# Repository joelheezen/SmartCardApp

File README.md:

# SmartCardApp
App to add barcodes to a smartdevice

# reading the saved data
use sharedPreferences to get the StringSet this gets a list in the following format:

```
val sharedPref = activity?.getPreferences(Context.MODE_PRIVATE) ?:return
val L = sharedPref.getStringSet("barcodes", HashSet()) // L = ("name0|number0|format0", "name1|number1|format1", ...etc)
```

then split using a delimiter like so:

```
L.forEach{
    val str = it
    val delimiter = "|"
    val values = str.split(delimiter)
    values[0] = name
    values[1] = number
    values[2] = format
    }
```
 
# barcode formats

barcodes are returned as an int, so for example, EAN-13 is denoted as 32

https://developers.google.com/android/reference/com/google/mlkit/vision/barcode/common/Barcode#FORMAT_EAN_13

check the link for explanation and complete formats compatible with this scanner.

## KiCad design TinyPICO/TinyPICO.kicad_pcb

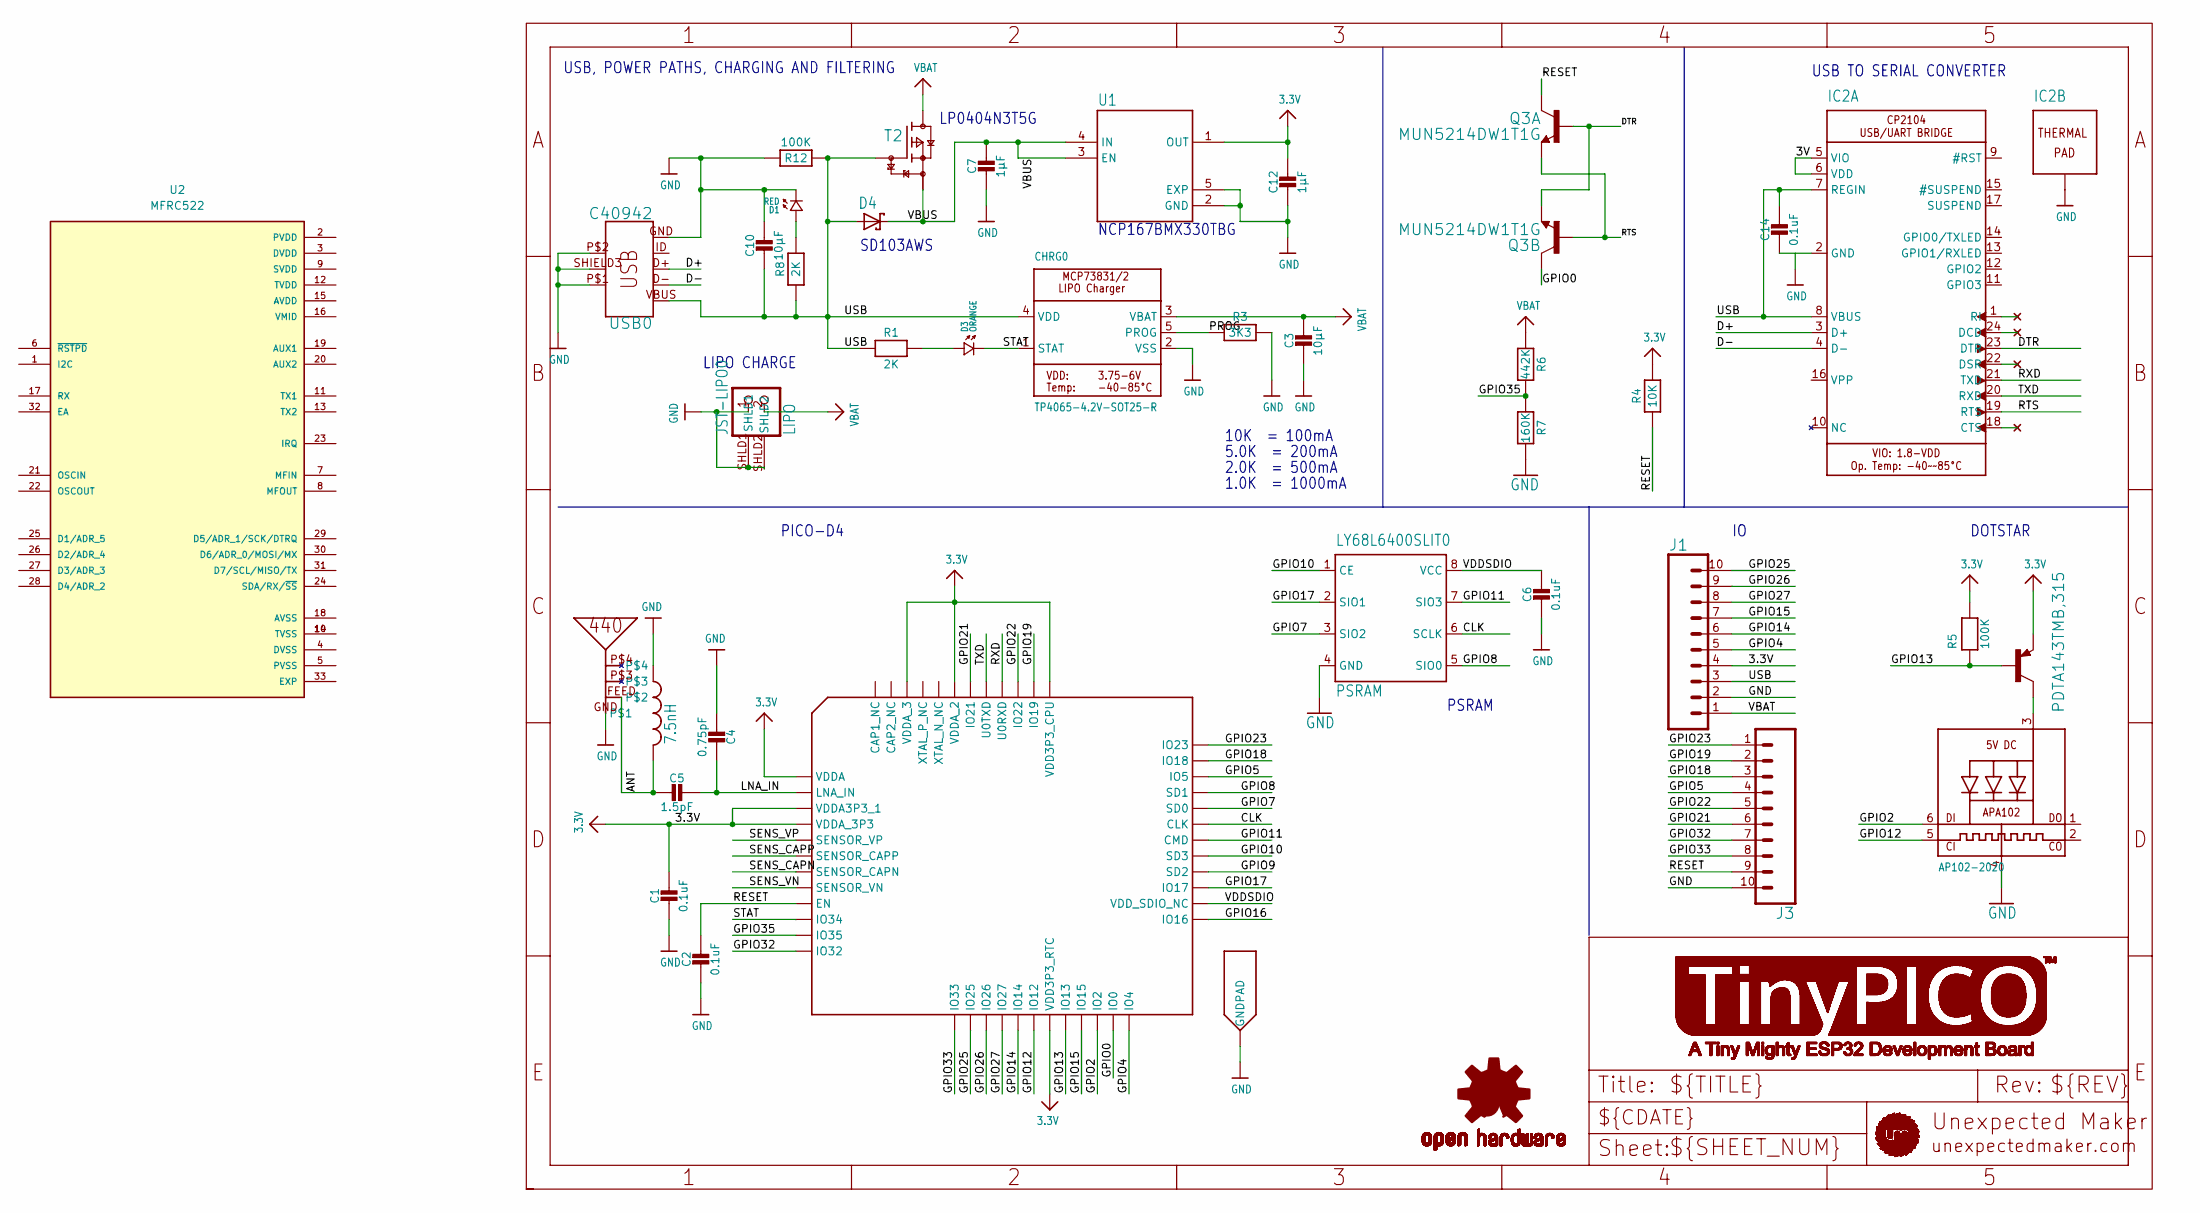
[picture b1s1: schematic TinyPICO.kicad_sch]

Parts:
C1, C2, C6, C14: 0.1uF; _0402MP
C3, C10: 10µF; _0603MP
C4: 0.75pF; _0402MP
C5: 1.5pF; _0402MP
C7, C12: 1µF; _0402MP
CHRG0: TP4065-4.2V-SOT25-R; SOT23-5
D1: RED; 0402.LED
D3: ORANGE; 0402.LED
D4: BAT60J; SOD323_ST
IC2: CP2104; MICROBUILDER_QFN24_4MM_SMSC
J1, J3: TINYPICO_HEADER_10NO_SILK_PTH_FEMALE; 1X10_NO_SILK
JST-LIPO0: LIPO; JSTPH2
L1: 7.5nH; RESC0402_N
LED1: AP102-2020; MICROBUILDER_APA102_2020
LOGO1: OSHW-LOGOS; OSHW-LOGO-S
LY68L6400SLIT0: PSRAM; SOP8
PDTA143TMB,315: TINYPICO-PNPMB; SOT883(B)
PICO-D4: ESP32-PICO-D4; PICO-D4-QFN48
Q3: MUN5214DW1T1G; DUAL_NPN_SC70-6
R1, R8: 2K; _0402MP
R3: 3K3; _0402MP
R4: 10K; _0402MP
R5, R12: 100K; _0402MP
R6: 442K; _0402MP
R7: 160K; _0402MP
T2: TINYPICO-P-FETMB; SOT883(B)
U1: NCP170AMX300TCG; VREG_NCP170AMX300TCG
U2: MFRC522; QFN50P500X500X100-33N; PARTREV 3.9
U$8: PRO-OB-440
USB0: C40942; USB-B-MICRO-SMD

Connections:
3.3V: C1.1, C12.1, J1.4, PDTA143TMB,315.2 (E), PICO-D4.1 (VDDA), PICO-D4.3 (VDDA3P3_1), PICO-D4.4 (VDDA_3P3), PICO-D4.19 (VDD3P3_RTC), PICO-D4.37 (VDD3P3_CPU), PICO-D4.43 (VDDA_2), PICO-D4.46 (VDDA_3), R4.2, R5.2, U1.1 (OUT)
3V: LY68L6400SLIT0.7 (SIO3), PICO-D4.30 (CMD)
ANT: C5.2, L1.2, U$8.FEED
CLK: LY68L6400SLIT0.6 (SCLK), PICO-D4.31 (CLK)
D+: IC2.3 (D+), USB0.D+
D-: IC2.4 (D-), USB0.D-
DTR: IC2.23 (DTR), Q3.1 (E), Q3.5 (B)
GND: C1.2, C2.2, C3.2, C4.2, C6.2, C7.2, C10.1, C12.2, C14.2, CHRG0.2 (VSS), D1.P$2 (2), IC2.2 (GND), IC2.THERM (TP), J1.2, J3.10, JST-LIPO0.1, JST-LIPO0.SHLD1, JST-LIPO0.SHLD2, L1.1, LED1.4 (GND), LY68L6400SLIT0.4 (GND), PICO-D4.EXP (GNDPAD), R3.2, R7.2, R12.2, U1.2 (GND), U1.5 (EXP), U$8.GND, USB0.GND, USB0.P$1 (SHIELD1), USB0.P$2 (SHIELD2), USB0.SHIELD3 (SHIELD)
GND2: PICO-D4.28 (SD2)
GND4: IC2.5 (VIO), IC2.6 (VDD)
GND6: LY68L6400SLIT0.1 (CE), PICO-D4.29 (SD3)
GND8: LY68L6400SLIT0.3 (SIO2), PICO-D4.32 (SD0)
GPIO0: PICO-D4.23 (IO0), Q3.6 (C)
GPIO2: LED1.6 (DI), PICO-D4.22 (IO2)
GPIO4: J1.5, PICO-D4.24 (IO4)
GPIO5: J3.4, PICO-D4.34 (IO5)
GPIO7: D3.P$1 (1), R1.2
GPIO9: LY68L6400SLIT0.5 (SIO0), PICO-D4.33 (SD1)
GPIO10: LED1.3 (VDD), PDTA143TMB,315.3 (C)
GPIO11: C6.1, LY68L6400SLIT0.8 (VCC), PICO-D4.26 (VDD_SDIO_NC)
GPIO12: LED1.5 (CKI), PICO-D4.18 (IO12)
GPIO13: PDTA143TMB,315.1 (B), PICO-D4.20 (IO13), R5.1
GPIO14: J1.6, PICO-D4.17 (IO14)
GPIO15: J1.7, PICO-D4.21 (IO15)
GPIO16: PICO-D4.25 (IO16)
GPIO17: LY68L6400SLIT0.2 (SIO1), PICO-D4.27 (IO17)
GPIO18: J3.3, PICO-D4.35 (IO18)
GPIO19: J3.2, PICO-D4.38 (IO19)
GPIO21: J3.6, PICO-D4.42 (IO21)
GPIO22: J3.5, PICO-D4.39 (IO22)
GPIO23: J3.1, PICO-D4.36 (IO23)
GPIO25: J1.10, PICO-D4.14 (IO25)
GPIO26: J1.9, PICO-D4.15 (IO26)
GPIO27: J1.8, PICO-D4.16 (IO27)
GPIO32: J3.7, PICO-D4.12 (IO32)
GPIO33: J3.8, PICO-D4.13 (IO33)
GPIO35: PICO-D4.11 (IO35), R6.2, R7.1
LNA_IN: C4.1, C5.1, PICO-D4.2 (LNA_IN)
unnamed: D1.P$1 (1), R8.2
unnamed: U2.10 (TVSS), U2.14 (TVSS)
PROG: CHRG0.5 (PROG), R3.1
RESET: C2.1, J3.9, PICO-D4.9 (EN), Q3.3 (C), R4.1
RTS: IC2.19 (RTS), Q3.2 (B), Q3.4 (E)
RXD: IC2.21 (TXD), PICO-D4.40 (U0RXD)
SENS_CAPN: PICO-D4.7 (SENSOR_CAPN)
SENS_CAPP: PICO-D4.6 (SENSOR_CAPP)
SENS_VN: PICO-D4.8 (SENSOR_VN)
SENS_VP: PICO-D4.5 (SENSOR_VP)
STAT: CHRG0.1 (STAT), D3.P$2 (2), PICO-D4.10 (IO34)
TXD: IC2.20 (RXD), PICO-D4.41 (U0TXD)
USB: C10.2, C14.1, CHRG0.4 (VDD), D4.A, IC2.7 (REGIN), IC2.8 (VBUS), J1.3, R1.1, R8.1, R12.1, T2.1 (G), USB0.VBUS
VBAT: C3.1, CHRG0.3 (VBAT), J1.1, JST-LIPO0.2, R6.1, T2.3 (D)
VBUS: C7.1, D4.C, T2.2 (S), U1.3 (EN), U1.4 (IN)

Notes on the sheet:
5.0K = 200mA
LP0404N3T5G
LIPO CHARGE
2.0K = 500mA
PSRAM
PICO-D4
USB, POWER PATHS, CHARGING AND FILTERING
10K = 100mA
NCP167BMX330TBG
DOTSTAR
SD103AWS
USB TO SERIAL CONVERTER
1.0K = 1000mA

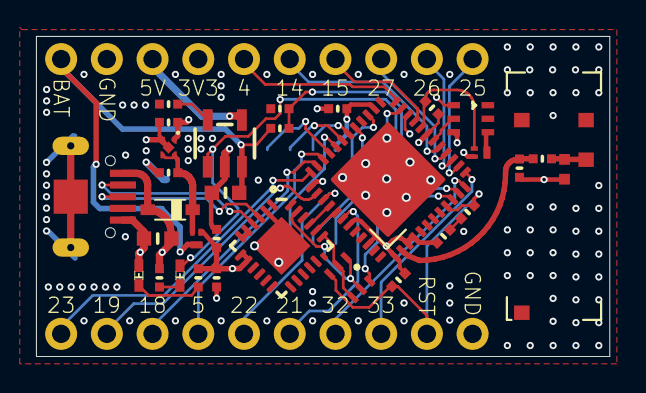
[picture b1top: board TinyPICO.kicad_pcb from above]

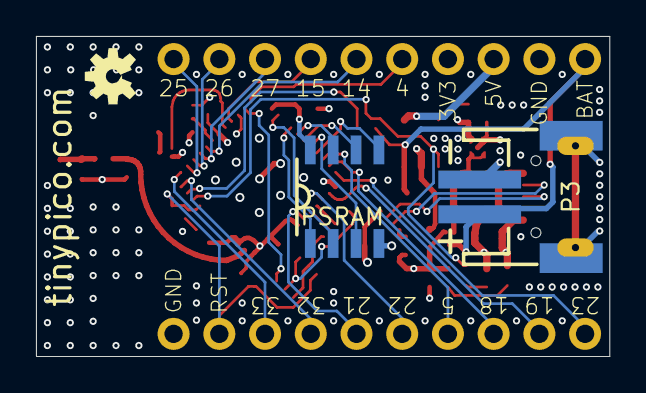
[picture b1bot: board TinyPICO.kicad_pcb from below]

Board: 4 copper layers, 31.9 x 17.8 mm, 37 parts (3 on the bottom side), 46 nets.

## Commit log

2023-11-20 Added scanner and snackbar display to show barcode display value
2023-11-23 change folder structure
2023-11-23 scanner now takes data from one fragment to another
2023-11-23 added code39 func
2023-11-23 started on upc
2023-11-24 nfc working
2023-11-24 cchanges
2023-11-24 fixed fragments
2023-11-27 Adding barcode now takes you to save screen, save works with name and number. Cards display on first page
2023-11-28 added format to save data, also displaying format in firstfragment. Untested
2023-11-28 added way to delete barcode via new fragment. untested since avd doesnt work on laptop.
2023-11-28 one line of code to make cards taller to better facilitate clicking on them. cant test layout yet
2023-11-28 changed README.md with little bit of info
2023-11-28 forgot to declare sharedPref in README.md
2023-11-28 noticed error in README.md
2023-11-28 added constraints to thirdfragment
2023-11-28 Shows barcode,name and format. clicking on the card gets you to new fragment where you can delete the entry. next step is to be able to edit it in the same screen.
2023-11-28 working mifare writing
2023-12-01 small changes to layouts, edited card.xml in order to add it to scrollview when a new code is added. Still needs the code to insert it
2023-12-01 added alertdialog to delete, so no accidental deletes
2023-12-01 removed some errors
2023-12-01 Changed delimiter to better format websites and other formats
2023-12-01 added else to MainActivity in order to only get one toast on startup, this toast indicates whether or not scan module is installed. This is because of a google bug not installing the required depende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
2023-12-04 adding in xml files via inflate works, now styling should be lot easier to manage
2023-12-05 ftest
2023-12-05 test
2023-12-05 TEST TEST TEST
2023-12-05 PCB design KiCad
2023-12-05 remove test files
2023-12-08 edited readme to reflect current code
2023-12-08 added pn532 func
2023-12-18 transfer working
2023-12-18 integrated nfc func into app
2023-12-21 added colour scheme and general cleanup of UI, still needs work
2023-12-22 small changes to sizing, working on dynamic themes
2023-12-22 removed theme since untested
2023-12-22 mifare reading writing working
2024-01-12 data transfer done :
2024-01-18 Added check to ensure name length is not too long
2024-01-18 cards can be save now
2024-01-22 code works with button now
2024-01-23 eeprom works now
2024-01-25 added schematic
2024-01-29 changed to analogpin
2024-01-29 final working code
